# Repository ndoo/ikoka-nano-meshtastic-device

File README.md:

# Ikoka Nano Meshtastic Device

A Meshtastic device based on the [Seeed Studio XIAO nRF52840](https://www.seeedstudio.com/Seeed-XIAO-BLE-nRF52840-p-5201.html) and EBYTE E22-XXXMXXS series LoRa modules. Pinout matches the [Meshtastic xiao_ble variant](https://github.com/meshtastic/firmware/tree/master/variants/xiao_ble).

The focus is on small size without an onboard display or buttons, meaning it must be used with [Meshtastic client software](https://meshtastic.org/docs/software/), or as a remote repeater managed with [remote node administration](https://meshtastic.org/docs/configuration/remote-admin/).

## Connectors

* USB-C for power and data
* Qwiic connector for I²C sensors
* Battery connectors (PicoBlade 1.25-2P)
* Solar connector (PicoBlade 1.25-2P, 4.45 to 6.45 V - BQ25100 charge IC)

## Libraries Used

* [SnapMagic E22-900M30S footprint & symbol](https://www.snapeda.com/parts/E22-900M30S/EBYTE/view-part/)
* [SparkFun KiCad Libraries](https://github.com/sparkfun/SparkFun-KiCad-Libraries)
* [SeeedStudio OPL KiCad Library](https://github.com/ndoo/OPL_Kicad_Library/tree/xiao-ble-symbols) (forked to add missing XIAO nRF5240 symbol)

## Building One

### Software Required

* The files were created in [KiCad](https://www.kicad.org/) 8
* Clone this git repository recursively, i.e. with `--recursive`

### Ordering PCBs

* Generate the production files
  * Install [kicad-jlcpcb-tools](https://github.com/Bouni/kicad-jlcpcb-tools)
  * Open the PCB file
  * Tools -> External Plugins -> JLCPCB Tools
  * Look over the Bill of Materials list and perform any substitutions required
  * Click Generate
* Order the PCBs
  * Use the Gerbers, BOM and CPL files in `jlcpcb/production_files`
  * Default 1.6mm 2-layer PCB settings should work well, this PCB passes DRC based on JLCPCB specifications (other than the silkscreen of XIAO module being clipped by the PCB edge)

### Ordering Components

* Check the exported BOM file in `jlcpcb/production_files`

### Assembling the PCB

I suggest PCBA, but I used handsoldering pads and all SMDs are 0603 or larger so can be hand-soldered.

1. Solder the SMD components
   * The larger (0805) capacitors go closer to the USB-C connector end of the PCB
2. Solder the connectors
3. Solder the XIAO BLE
   1. It helps to tin the BAT+ pad first, it will help ensure successful soldering through the back. Remove excess solder so that the pad is flat, otherwise the XIAO will not sit flush
   2. Solder one pad first then verify all pads and the battery hole are lined up well, adjust the alignment if necessary
   3. Solder one more pad diagonally opposite, double check the alignment of the pads
   4. Solder the rear hole that goes to the BAT+ pad
   5. Solder the rest of the pads
   6. Test that the XIAO is able to power up from the battery and that charging works (a yellow LED will light up if the battery is charging), you won't be able to access the BAT+ pad once the E22 module is soldered
4. Solder the E22-900M30S module

### Flashing Meshtastic Firmware

#### Pre-built Binaries (Unofficial)

1. [Custom Meshtastic builds web installer](https://mrekin.duckdns.org/flasher/)
2. Select your device -> Xiao BLE
3. Select firmware version -> Pick the latest release
4. Select update or reinstall -> Update device (usually works fine, but if Meshtastic does not start after a few seconds, wipe and reinstall)
5. Download UF2
6. Connect USB-C to PC, double-tap the reset button
7. Drop UF2 file into XIAO-SENSE USB volume

#### Building from Source

Follow the instructions at [meshtastic/firmware/variants/diy/xiao_ble/](https://github.com/meshtastic/firmware/tree/master/variants/diy/xiao_ble).

### Enclosure

A snap-fit 3D printable enclosure is available in the `enclosures` folder. **This has not been updated for the latest board design ([2b17a53](https://github.com/ndoo/ikoka-nano-meshtastic-device/commit/2b17a53b4cfc0f9a9a845ffaf8d8353723f1d552)).**

## PCB Images

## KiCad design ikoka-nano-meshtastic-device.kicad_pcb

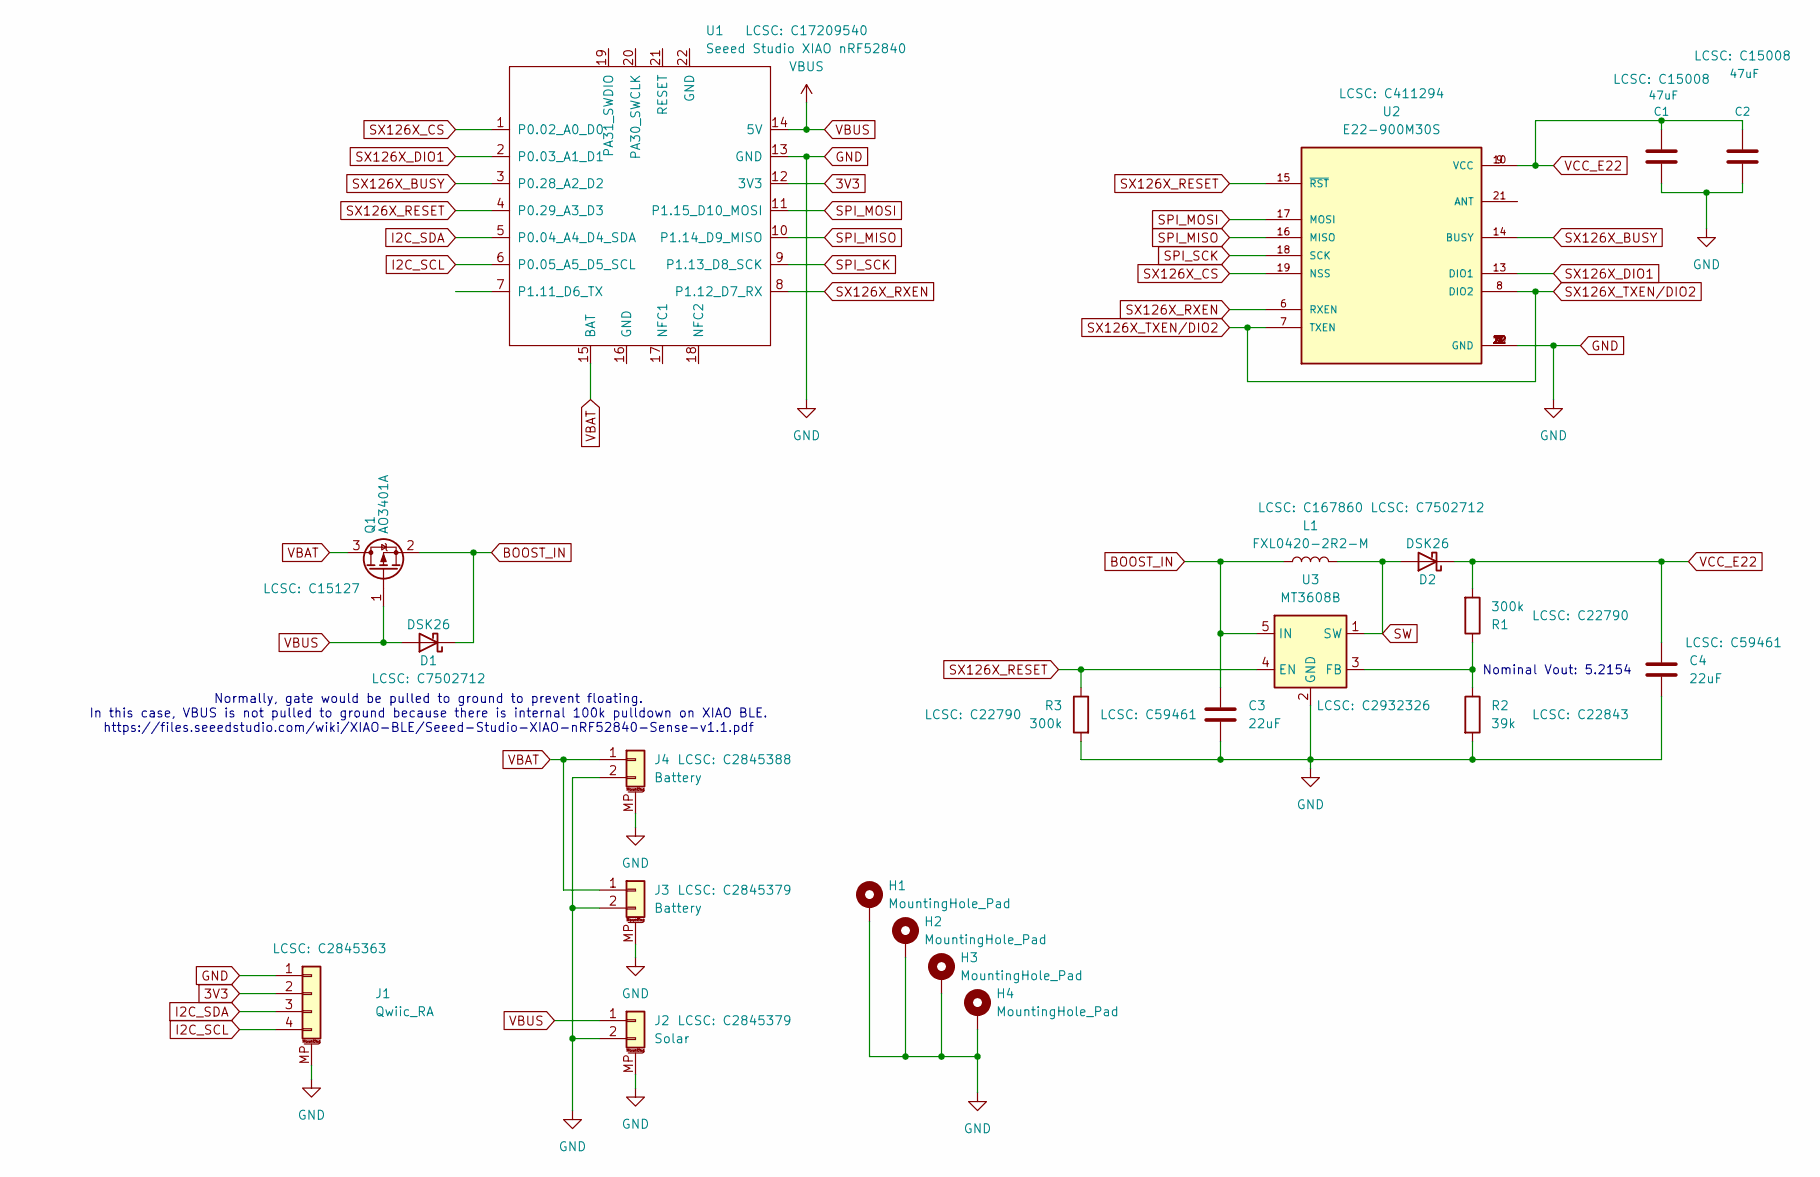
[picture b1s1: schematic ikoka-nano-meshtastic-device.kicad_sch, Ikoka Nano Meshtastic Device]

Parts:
C1, C2: 47uF; C_0805_2012Metric_Pad1.18x1.45mm_HandSolder; MPN CL31A107MQHNNNE; LCSC C15008
C3, C4: 22uF; C_0603_1608Metric_Pad1.08x0.95mm_HandSolder; MPN CL10A226MQ8NRNC; LCSC C59461
D1, D2: DSK26; D_SOD-123F; LCSC C7502712
H1, H2, H3, H4: MountingHole_Pad; MountingHole_2.7mm_M2.5_Pad_Via
J1: Qwiic_RA; JST_SH_SM04B-SRSS-TB_1x04-1MP_P1.00mm_Horizontal; LCSC C2845363
J2: Solar; Molex_PicoBlade_53261-0271_1x02-1MP_P1.25mm_Horizontal; LCSC C2845379
J3: Battery; Molex_PicoBlade_53261-0271_1x02-1MP_P1.25mm_Horizontal; LCSC C2845379
J4: Battery; Molex_PicoBlade_53398-0271_1x02-1MP_P1.25mm_Vertical; LCSC C2845388
L1: FXL0420-2R2-M; L_Changjiang_FXL0420; MPN SMMS0650-220M; LCSC C167860
Q1: AO3401A; SOT-23; LCSC C15127
R1, R3: 300k; R_0603_1608Metric_Pad0.98x0.95mm_HandSolder; MPN 0603WAF1502T5E; LCSC C22790
R2: 39k; R_0603_1608Metric_Pad0.98x0.95mm_HandSolder; MPN 0603WAF1871T5E; LCSC C22843
U1: Seeed Studio XIAO nRF52840; XIAO-nRF52840-SMD_Handsoldering; LCSC C17209540
U2: E22-900M30S; XCVR_E22-900M30S; PARTREV 1.2; LCSC C411294
U3: MT3608B; SOT-23-6; LCSC C2932326

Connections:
3V3: J1.2, U1.12 (3V3)
BOOST_IN: C3.1, D1.1 (K), L1.1, Q1.2 (S), U3.5 (IN)
GND: C1.1, C2.1, C3.2, C4.2, H1.1, H2.1, H3.1, H4.1, J1.1, J1.MP (MountPin), J2.2, J2.MP (MountPin), J3.2, J3.MP (MountPin), J4.2, J4.MP (MountPin), R2.2, R3.2, U1.13 (GND), U2.1 (GND), U2.2 (GND), U2.3 (GND), U2.4 (GND), U2.5 (GND), U2.11 (GND), U2.12 (GND), U2.20 (GND), U2.22 (GND), U3.2 (GND)
I2C_SCL: J1.4, U1.6 (P0.05_A5_D5_SCL)
I2C_SDA: J1.3, U1.5 (P0.04_A4_D4_SDA)
unnamed: R1.1, R2.1, U3.3 (FB)
SPI_MISO: U1.10 (P1.14_D9_MISO), U2.16 (MISO)
SPI_MOSI: U1.11 (P1.15_D10_MOSI), U2.17 (MOSI)
SPI_SCK: U1.9 (P1.13_D8_SCK), U2.18 (SCK)
SW: D2.2 (A), L1.2, U3.1 (SW)
SX126X_BUSY: U1.3 (P0.28_A2_D2), U2.14 (BUSY)
SX126X_CS: U1.1 (P0.02_A0_D0), U2.19 (NSS)
SX126X_DIO1: U1.2 (P0.03_A1_D1), U2.13 (DIO1)
SX126X_RESET: R3.1, U1.4 (P0.29_A3_D3), U2.15 (~RST), U3.4 (EN)
SX126X_RXEN: U1.8 (P1.12_D7_RX), U2.6 (RXEN)
SX126X_TXEN/DIO2: U2.7 (TXEN), U2.8 (DIO2)
VBAT: J3.1, J4.1, Q1.3 (D), U1.15 (BAT)
VBUS: D1.2 (A), J2.1, Q1.1 (G), U1.14 (5V)
VCC_E22: C1.2, C2.2, C4.1, D2.1 (K), R1.2, U2.9 (VCC), U2.10 (VCC)

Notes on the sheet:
Nominal Vout: 5.2154
Normally, gate would be pulled to ground to prevent floating. In this case, VBUS is not pulled to ground because there is internal 100k pulldown on XIAO BLE. https://files.seeedstudio.com/wiki/XIAO-BLE/Seeed-Studio-XIAO-nRF52840-Sense-v1.1.pdf

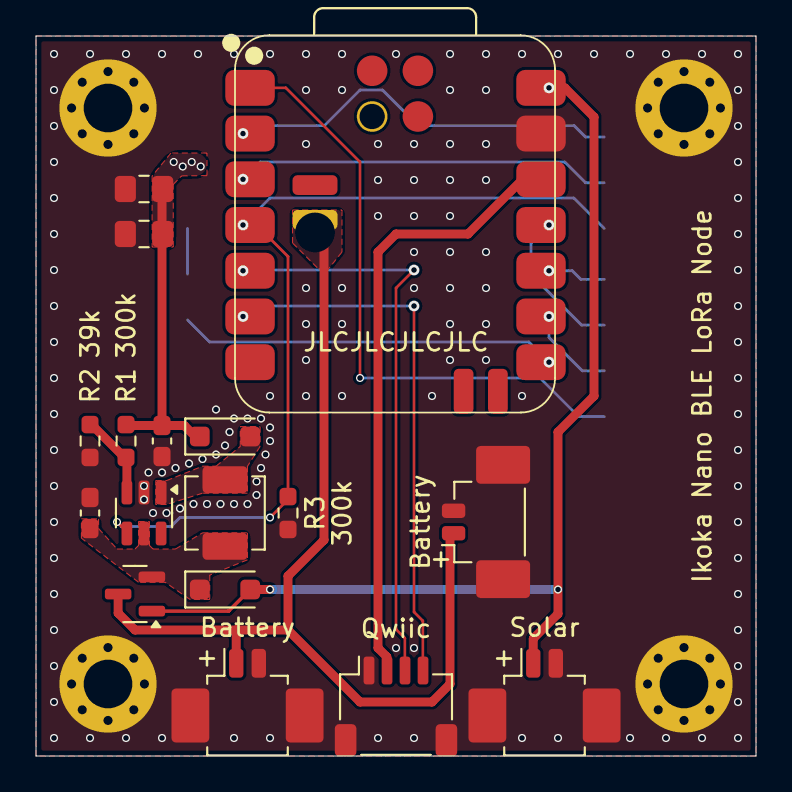
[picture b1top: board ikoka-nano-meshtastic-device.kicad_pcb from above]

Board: 2 copper layers, 40.0 x 40.0 mm, 22 parts (1 on the bottom side), 19 nets.

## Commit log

2024-03-23 Update README.md with some build instructions and add CAM file
2024-03-23 Update README and add PCB images
2024-03-23 Redesign board because the E22-900M22S footprint from SnapMagic was much smaller than the actual module size; add solar 5V connector; reduce Qwiic connectors to just one.
2024-03-23 Move some values to names layer to ensure JLCPCB CAM generates silkscreen; hide U1/U2 value under components
2024-03-23 Update README.md with flashing instructions
2024-03-23 Add project name and ndoo.sg to board front
2024-03-23 Update PCB images
2024-03-23 Update schematic with LCSC part numbers
2024-03-23 Update board images to be non-perspective views
2024-03-23 Add generated Gerbers/BOM for JLCPCB
2024-05-09 Power EBYTE E22 module from 5V and remove JST-PH 2.0 connectors
    Power EBYTE E22 module from 5V because VBAT results in very poor transmit power.
    Remove JST connectors since the device no longer functions without 5V.
2024-05-09 Add kicad-render GitHub action
    Add kicad-render GitHub action from [linalinn/kicad-render](https://github.com/linalinn/kicad-render)
2024-05-09 Update README for KiCad 8 and rendered images
2024-05-09 Update footprints table
2024-05-09 Update .gitignore to ignore KiCad 8 lock files
2024-05-11 Update README.md and remove repo board images
2024-05-23 Update README to remove reference to battery and solar power.
2024-05-23 enclosure: Add 3D printable enclosure and update README
2024-05-23 Remove gerbers, use README instructions to generate them on demand
2024-11-28 Add LICENSE
2024-11-28 Add Molex Picoblade 1.25x2 connectors for VBAT and VBUS, add load switch for E22 module power
2024-11-28 Add missing D1 footprint and update PCB; add LCSC part numbers; remove gerbers
2024-11-28 Increase VBAT via size and add teardrop
2024-11-28 Fix part attributes for LCSC PN and make compatible with latest JLCPCB fabrication toolkit
2024-11-29 Add LCSC PN display for C1, clean up production folder again
2024-12-03 Sync submodules
2024-12-03 Branch Seeed OPL Kicad library to modify XIAO nRF52840 Library
2024-12-03 Update Seeed XIAO nRF52840 with BAT+ PTH pad
2024-12-10 Switch back to SparkFun Qwiic symbol/footprint, run DRC, fix 3D models
2024-12-10 Rebase XIAO BLE hand soldering symbol/footprint on upstream
2025-01-14 Add 5.4V boost converter circuit, use more JLCPCB basic parts, make PCB square, add internal battery connector
2025-01-14 Use AO3401A PMOS which is JLCPCB basic part
2025-02-27 Sync symbol libraries
2025-07-10 Add カモノハシのイコちゃん silkscreen
2025-07-10 chore: Sync footprint libraries
2025-07-10 chore(GitHub): Fix pcb_image workflow
2025-07-10 chore: Update .gitignore
2025-07-10 feat: Improve DC-DC converter and power path
    - Update R1 and R2 resistors to match Ikoka Handheld values (300kΩ, 39kΩ respectively)
    - Change E22 capacitors to 2x 47µF instead of 2x 100µF
    - Change P-MOSFET load switch to switch input to DC-DC boost so that E22 supply is constant even when switching to USB power
    - Add 300k pulldown on MT3608L enable pin to prevent it floating when Meshtastic firmware is not running
    - Layout for above changes
    - Move connectors flush with PCB edge
2025-07-10 chore: Use correct Kicad connector symbols and ground MountingPins
2025-07-10 fix(pcbnew): Set XIAO footprint type to SMD
2025-07-10 fix(pcbnew): XIAO 3dmodel path was incorrect
2025-07-13 Update README.md
    - Update "Assembling the PCB"
    - Update "Flashing Meshtastic Firmware" (fixes #10)
2025-07-15 feat: Improve boost converter part selection
    - Change inductor from 22uH FNR4026S220MT to 2.2uH FXL0420-2R2-M
    - Change MT3608L to MT3608B
